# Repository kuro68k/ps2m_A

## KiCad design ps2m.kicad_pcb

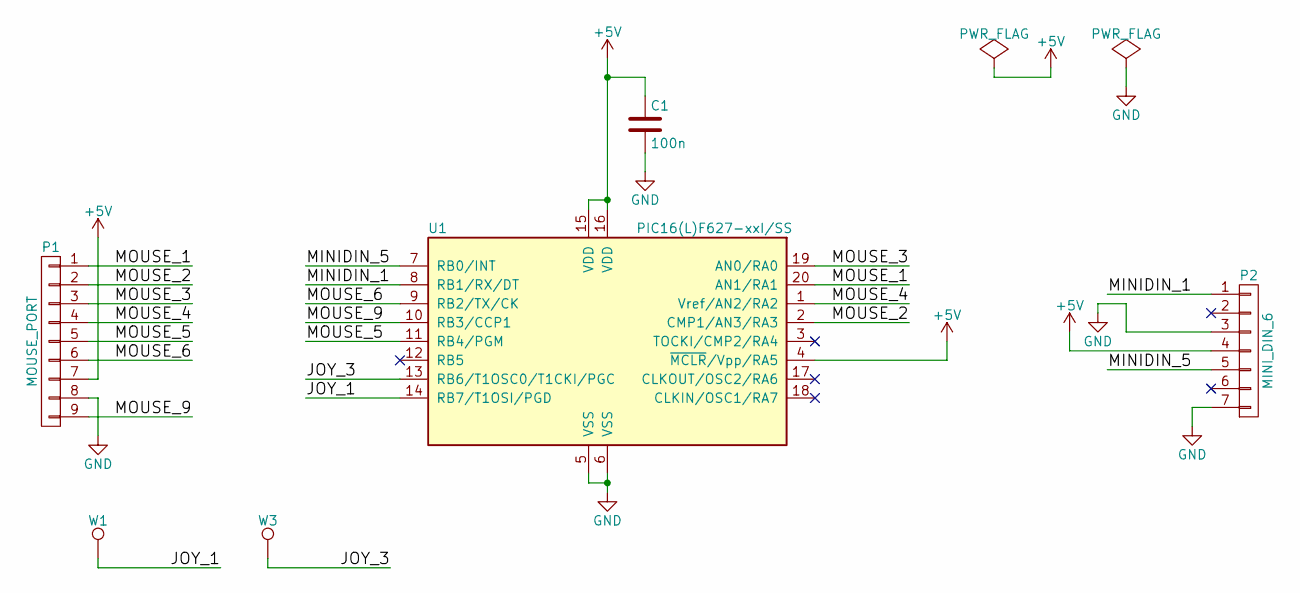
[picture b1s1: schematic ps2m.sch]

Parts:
C1: 100n; C_0603_HandSoldering
P1: MOUSE_PORT; DB9F-RA-TH-EUR
P2: MINI_DIN_6; miniDIN-6-TH-Wrap
U1: PIC16(L)F627-xxI/SS; SSOP-20_5.3x7.2mm_Pitch0.65mm
W1, W3: TEST_1P; Measurement_Point_Square-SMD-Pad_Small

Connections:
+5V: C1.1, P1.7, P2.4, U1.4 (~MCLR~/Vpp/RA5), U1.15 (VDD), U1.16 (VDD)
/JOY_1: U1.14 (RB7/T1OSI/PGD), W1.1
/JOY_3: U1.13 (RB6/T1OSC0/T1CKI/PGC), W3.1
/MINIDIN_1: P2.1, U1.8 (RB1/RX/DT)
/MINIDIN_5: P2.5, U1.7 (RB0/INT)
/MOUSE_1: P1.1, U1.20 (AN1/RA1)
/MOUSE_2: P1.2, U1.2 (CMP1/AN3/RA3)
/MOUSE_3: P1.3, U1.19 (AN0/RA0)
/MOUSE_4: P1.4, U1.1 (Vref/AN2/RA2)
/MOUSE_5: P1.5, U1.11 (RB4/PGM)
/MOUSE_6: P1.6, U1.9 (RB2/TX/CK)
/MOUSE_9: P1.9, U1.10 (RB3/CCP1)
GND: C1.2, P1.8, P2.3, P2.7, U1.5 (VSS), U1.6 (VSS)

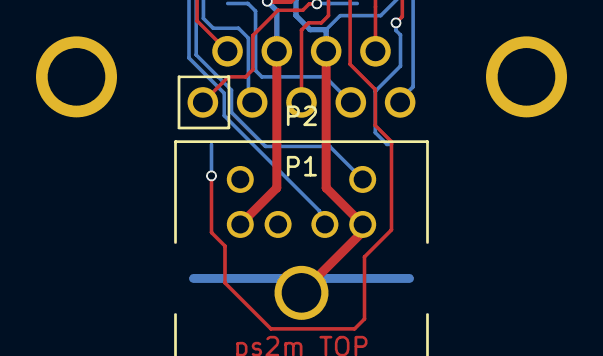
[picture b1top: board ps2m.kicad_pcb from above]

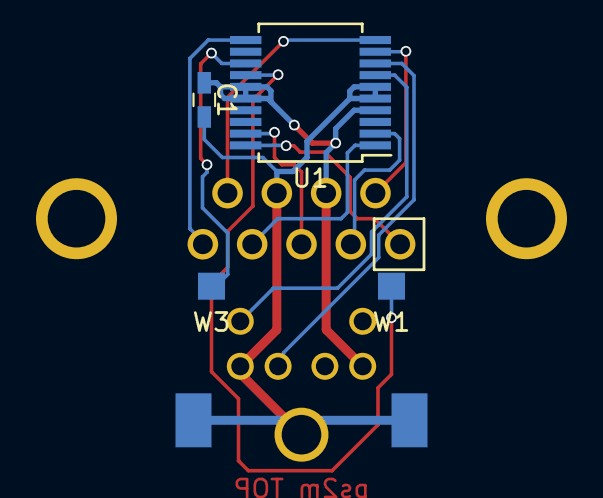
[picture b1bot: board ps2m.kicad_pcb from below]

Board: 2 copper layers, 6 parts (4 on the bottom side), 13 nets.

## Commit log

2017-07-07 :lollipop: Added .gitattributes & .gitignore files
2017-07-07 GND connection
2017-07-07 Silkscreen
2017-07-07 Corrected fab layer for DB9
2017-07-08 Rounded edges of PCB, TOP side note
2017-07-09 Corrected silkscreen
2017-07-09 Plot
2017-07-09 Imperial drill file for Seeed
2017-07-10 Part numbers for BOM
2017-07-10 Added BOM
2017-07-10 removed pogo pins
2017-08-12 Fixed MiniDIN footprint and narrowed board to accomodate
2017-08-13 Updated gerbers
2017-08-14 V1.1 improved tracking/placement
2017-08-17 Fixed solder mask on bottom layer for MiniDIN socket
